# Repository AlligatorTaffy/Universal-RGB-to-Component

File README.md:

# Universal RGB to Component
 
Another CadSoft Eagle project.  This is a circuit that will convert raw RGB signals to a Component (YPbPr) signal since most USA TVs adopted the Component inputs.

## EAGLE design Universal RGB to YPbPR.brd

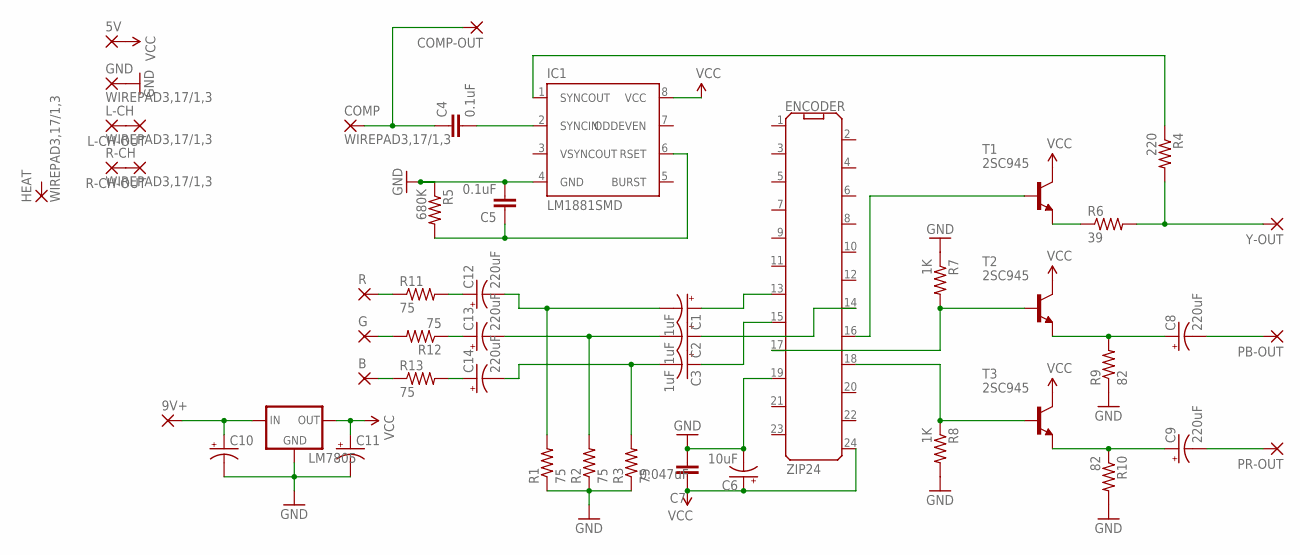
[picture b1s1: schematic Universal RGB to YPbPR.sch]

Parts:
5V, 9V+: WIREPAD3,17/1,3; 3,17/1,3
B: WIREPAD3,17/1,3; 3,17/1,3
C1, C2, C3: 1uF; CPOL-RADIAL-10UF-25V
C4, C5: 0.1uF; C025-024X044
C6: 10uF; CPOL-RADIAL-10UF-25V
C7: 0.047uF; C025-024X044
C8, C9, C12, C13, C14: 220uF; CPOL-RADIAL-1000UF-25V
C10, C11: CAP_POLPTH1; CPOL-RADIAL-100UF-25V
COMP: WIREPAD3,17/1,3; 3,17/1,3
COMP-OUT: WIREPAD3,17/1,3; 3,17/1,3
ENCODER: ZIP24
G: WIREPAD3,17/1,3; 3,17/1,3
GND: WIREPAD3,17/1,3; 3,17/1,3
HEAT: WIREPAD3,17/1,3; 3,17/1,3
IC1: LM1881SMD; SO08
L-CH: WIREPAD3,17/1,3; 3,17/1,3
L-CH-OUT: WIREPAD3,17/1,3; 3,17/1,3
LM7805: V_REG_78XX; DPAK
PB-OUT: WIREPAD3,17/1,3; 3,17/1,3
PR-OUT: WIREPAD3,17/1,3; 3,17/1,3
R: WIREPAD3,17/1,3; 3,17/1,3
R1, R2, R3, R11, R12, R13: 75; 0207/2V
R4: 220; 0207/2V
R5: 680K; 0207/2V
R6: 39; 0207/2V
R7, R8: 1K; 0207/2V
R9, R10: 82; 0207/2V
R-CH: WIREPAD3,17/1,3; 3,17/1,3
R-CH-OUT: WIREPAD3,17/1,3; 3,17/1,3
T1, T2, T3: 2SC945; TO92-ECB
Y-OUT: WIREPAD3,17/1,3; 3,17/1,3

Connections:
GND: C5.2, C6.2 (-), C7.2, C10.2 (-), C11.2 (-), ENCODER.19 (GND), GND.1, IC1.4 (GND), LM7805.4 (GND), R1.1, R2.1, R3.1, R5.1, R7.1, R8.2, R9.1, R10.2
unnamed: C8.1 (+), R9.2, T2.E
unnamed: C9.1 (+), R10.1, T3.E
unnamed: C9.2 (-), PR-OUT.1
unnamed: L-CH.1, L-CH-OUT.1
unnamed: R-CH.1, R-CH-OUT.1
unnamed: C8.2 (-), PB-OUT.1
unnamed: 9V+.1, C10.1 (+), LM7805.1 (IN)
unnamed: R.1, R11.1
unnamed: C4.2, IC1.2 (SYNCIN)
unnamed: C1.2 (-), C12.2 (-), R1.2
unnamed: C2.2 (-), C13.2 (-), R2.2
unnamed: C3.2 (-), C14.2 (-), R3.2
unnamed: G.1, R12.2
unnamed: B.1, R13.1
unnamed: C14.1 (+), R13.2
unnamed: C13.1 (+), R12.1
unnamed: C12.1 (+), R11.2
unnamed: C1.1 (+), ENCODER.13 (AR)
unnamed: C2.1 (+), ENCODER.14 (AG)
unnamed: C3.1 (+), ENCODER.15 (AB)
unnamed: C4.1, COMP.1, COMP-OUT.1
unnamed: ENCODER.16 (Y-OUT), T1.B
unnamed: ENCODER.17 (B-Y-OUT), R7.2, T2.B
unnamed: ENCODER.18 (R-Y-OUT), R8.1, T3.B
unnamed: IC1.1 (SYNCOUT), R4.1
unnamed: C5.1, IC1.6 (RSET), R5.2
unnamed: R6.1, T1.E
unnamed: R4.2, R6.2, Y-OUT.1
VCC: 5V.1, C6.1 (+), C7.1, C11.1 (+), ENCODER.24 (VCC), IC1.8 (VCC), LM7805.3 (OUT), T1.C, T2.C, T3.C

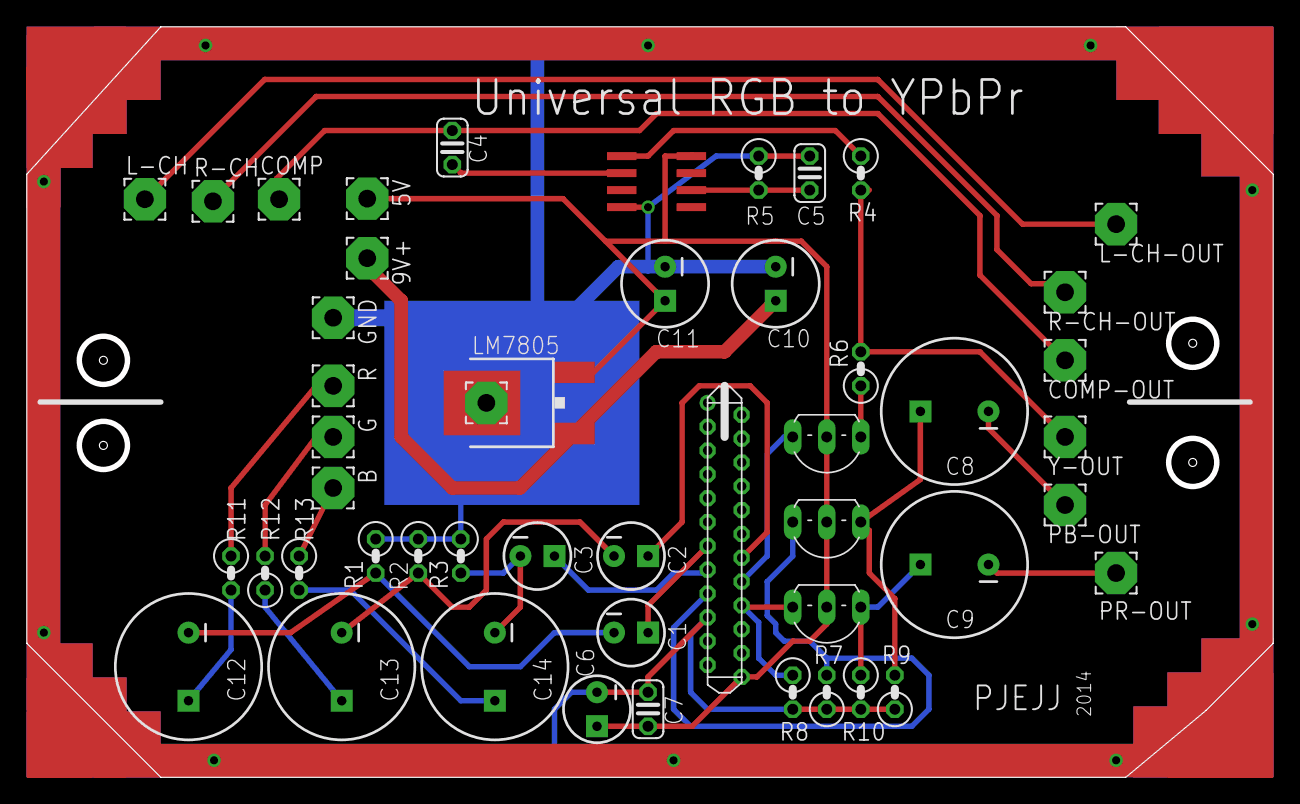
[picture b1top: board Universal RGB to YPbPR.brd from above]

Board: 2 copper layers, 92.6 x 55.6 mm, 49 parts (0 on the bottom side), 30 nets.

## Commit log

2023-05-29 Migrate to GitHub

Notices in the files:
parts and their libraries:
SparkFun-Capacitors: Licensing: Creative Commons ShareAlike 4.0 International - https://creativecommons.org/licenses/by-sa/4.0
